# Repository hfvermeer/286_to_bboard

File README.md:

# 286 to breadboard adapter
60-pin breadboard adapter for the 286 processor in PLCC-68 package

## Features
This slim design breadboard adapter for the 286 processor features the essential connections, descriptions, decoupling capacitors and even a small array of debugging leds for the system pin outputs. 

The debugging leds are optional, and may be left unpopulated if desired. The debugging leds may be switched off too by cutting the solder jumper 'JP1', or re-enabled again by soldering the bridge. It is enabled by default.

The adapter may also use J3 to provide power pins on the bottom side that directly connect to the breadboard power lines.

## Hardware Documentation

### Connections

#### J1 - Breadboard Jumper Header 1

Pin | Description
--- | -----------
1   | HLDA
2   | <ins>PEACK</ins>
3   | COD/<ins>INT</ins>
4   | <ins>Lock</ins>
5   | M//<ins>IO</ins>
6   | <ins>BHE</ins>
7   | <ins>S1</ins>
8   | <ins>S0</ins>
9   | D15
10  | D14
11  | D13
12  | D12
13  | D11
14  | D10
15  | D9
16  | D8
17  | D7
18  | D6
19  | D5
20  | D4
21  | D3
22  | D2
23  | D1
24  | D0
25  | <ins>ERROR</ins>
26  | <ins>BUSY</ins>
27  | CLK
28  | RESET
29  | GND
30  | VCC

#### J2 - Breadboard Jumper Header 2

Pin | Description
--- | -----------
1   | HOLD
2   | PEREQ
3   | NMI
4   | INTR
5   | <ins>READY</ins>
6   | GND
7   | A23
8   | A22
9   | A21
10   | A20
11  | A19
12  | A18
13  | A17
14  | A16
15  | A15
16  | A14
17  | A13
18  | A12
19  | A11
20  | A10
21  | A9
22  | A8
23  | A7
24  | A6
25  | A5
26  | A4
27  | A3
28  | A2
29  | A1
30  | A0

#### J3 - Breadboard Jumper Header 3 (Optional)

Pin | Description
--- | -----------
1   | VCC
2   | GND

### Bill of Materials (BOM)

Component type | Reference | Description | Quantity | Source and notes
-------------- | --------- | ----------- | -------- | ----------------
Capacitor | C1, C3, C4, C5 | 100nf, 0805 | 4 | 
Capacitor | C2 | 10uf, 0805 | 1 | 
Capacitor | C6 | 47nf, 0805 | 1 |
Capacitor | C7 | 100nf, 0402 | 1 | 
LED | D1, D2. D3, D4, D5, D6, D7, D8 | RED, 0603 | 8 |
Resistor | R1, R2. R3, R4, R5, R6, R7, R8 | 2k, 0402 | 8 |
Resistor | R9 | 1k, 0402 | 1 | 
Jumper | J1, J2 | Vertical, 2.54mm, SMT, pin1 left | 2 | 
Jumper | J3 | Vertical, 2.54mm, THT | 1 | 
IC | U1 | 74HC244, TSSOP-20 | 1 | 
Socket | UA1 | PLCC-68, SMT | 1 |

### Build Instructions

Hand solder under soldering microscope. The pads for connectors J1 and J2 contain via-in-pads. If using a stencil, these must be filled with tin prior to applying paste, otherwise they may wich up solder paste that is applied.

## Release Notes

### Changes

* Version 1.0.0
  * Add component Values
  * Correct 74HC240 to 74HC244 in schematic
  * Correct label descriptions for GND, CLK, VCC and RESET
  * Add anchor plate for pin headers
  * Add Gerbers

* Version 0.9.0
  * Initial Release

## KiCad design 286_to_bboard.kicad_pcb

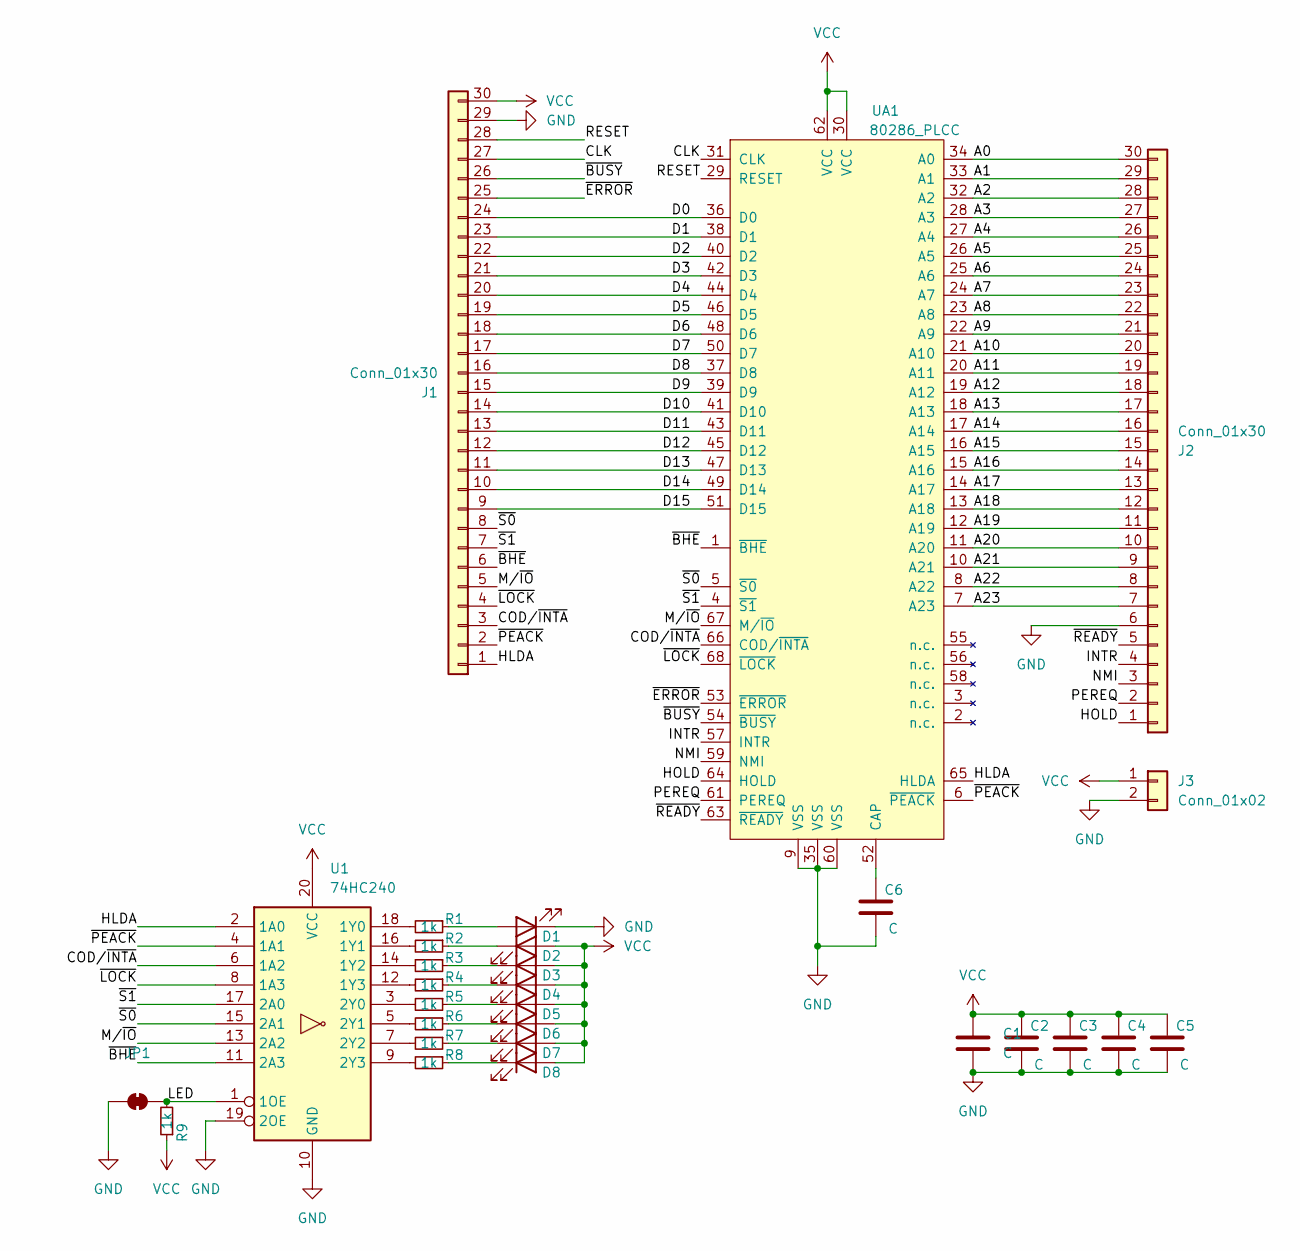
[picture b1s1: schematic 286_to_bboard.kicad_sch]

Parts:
C1, C2, C3, C4, C6: C; C_0805_2012Metric_Pad1.18x1.45mm_HandSolder
C5: C; C_0402_1005Metric_Pad0.74x0.62mm_HandSolder
D1, D2: RED; LED_0603_1608Metric
D3, D4, D5, D6, D7, D8: HLDA; LED_0603_1608Metric
J1, J2: Conn_01x30; PinHeader_1x30_P2.54mm_Vertical_SMD_Pin1Left
J3: Conn_01x02; PinHeader_1x02_P2.54mm_Vertical
JP1: Bridged; SolderJumper-2_P1.3mm_Bridged_RoundedPad1.0x1.5mm
R1, R2, R3, R4, R5, R6, R7, R8: 1k; R_0402_1005Metric
R9: 1k; R_0402_1005Metric_Pad0.72x0.64mm_HandSolder
U1: 74HC240
UA1: 80286_PLCC; PLCC-68_SMD-Socket

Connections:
/A0: J2.30, UA1.34 (A0)
/A1: J2.29, UA1.33 (A1)
/A2: J2.28, UA1.32 (A2)
/A3: J2.27, UA1.28 (A3)
/A4: J2.26, UA1.27 (A4)
/A5: J2.25, UA1.26 (A5)
/A6: J2.24, UA1.25 (A6)
/A7: J2.23, UA1.24 (A7)
/A8: J2.22, UA1.23 (A8)
/A9: J2.21, UA1.22 (A9)
/A10: J2.20, UA1.21 (A10)
/A11: J2.19, UA1.20 (A11)
/A12: J2.18, UA1.19 (A12)
/A13: J2.17, UA1.18 (A13)
/A14: J2.16, UA1.17 (A14)
/A15: J2.15, UA1.16 (A15)
/A16: J2.14, UA1.15 (A16)
/A17: J2.13, UA1.14 (A17)
/A18: J2.12, UA1.13 (A18)
/A19: J2.11, UA1.12 (A19)
/A20: J2.10, UA1.11 (A20)
/A21: J2.9, UA1.10 (A21)
/A22: J2.8, UA1.8 (A22)
/A23: J2.7, UA1.7 (A23)
/CLK: J1.27, UA1.31 (CLK)
/COD/~INTA: J1.3, U1.6 (1A2), UA1.66 (COD/~INTA)
/D0: J1.24, UA1.36 (D0)
/D1: J1.23, UA1.38 (D1)
/D2: J1.22, UA1.40 (D2)
/D3: J1.21, UA1.42 (D3)
/D4: J1.20, UA1.44 (D4)
/D5: J1.19, UA1.46 (D5)
/D6: J1.18, UA1.48 (D6)
/D7: J1.17, UA1.50 (D7)
/D8: J1.16, UA1.37 (D8)
/D9: J1.15, UA1.39 (D9)
/D10: J1.14, UA1.41 (D10)
/D11: J1.13, UA1.43 (D11)
/D12: J1.12, UA1.45 (D12)
/D13: J1.11, UA1.47 (D13)
/D14: J1.10, UA1.49 (D14)
/D15: J1.9, UA1.51 (D15)
/HLDA: J1.1, U1.2 (1A0), UA1.65 (HLDA)
/HOLD: J2.1, UA1.64 (HOLD)
/INTR: J2.4, UA1.57 (INTR)
/LED: JP1.2 (B), R9.2, U1.1 (1OE)
/M/~IO: J1.5, U1.13 (2A2), UA1.67 (M/~IO)
/NMI: J2.3, UA1.59 (NMI)
/PEREQ: J2.2, UA1.61 (PEREQ)
/RESET: J1.28, UA1.29 (RESET)
/~BHE: J1.6, U1.11 (2A3), UA1.1 (~BHE)
/~BUSY: J1.26, UA1.54 (~BUSY)
/~ERROR: J1.25, UA1.53 (~ERROR)
/~LOCK: J1.4, U1.8 (1A3), UA1.68 (~LOCK)
/~PEACK: J1.2, U1.4 (1A1), UA1.6 (~PEACK)
/~READY: J2.5, UA1.63 (~READY)
/~S0: J1.8, U1.15 (2A1), UA1.5 (~S0)
/~S1: J1.7, U1.17 (2A0), UA1.4 (~S1)
GND: C1.2, C2.2, C3.2, C4.2, C5.2, C6.2, D1.1 (K), J1.29, J2.6, J3.2, JP1.1 (A), U1.10 (GND), U1.19 (2OE), UA1.9 (VSS), UA1.35 (VSS), UA1.60 (VSS)
unnamed: D1.2 (A), R1.1
unnamed: D2.1 (K), R2.1
unnamed: D3.1 (K), R3.1
unnamed: D4.1 (K), R4.1
unnamed: D5.1 (K), R5.1
unnamed: D6.1 (K), R6.1
unnamed: D7.1 (K), R7.1
unnamed: D8.1 (K), R8.1
unnamed: R1.2, U1.18 (1Y0)
unnamed: R2.2, U1.16 (1Y1)
unnamed: R3.2, U1.14 (1Y2)
unnamed: R4.2, U1.12 (1Y3)
unnamed: R5.2, U1.3 (2Y0)
unnamed: R6.2, U1.5 (2Y1)
unnamed: R7.2, U1.7 (2Y2)
unnamed: R8.2, U1.9 (2Y3)
unnamed: C6.1, UA1.52 (CAP)
VCC: C1.1, C2.1, C3.1, C4.1, C5.1, D2.2 (A), D3.2 (A), D4.2 (A), D5.2 (A), D6.2 (A), D7.2 (A), D8.2 (A), J1.30, J3.1, R9.1, U1.20 (VCC), UA1.30 (VCC), UA1.62 (VCC)

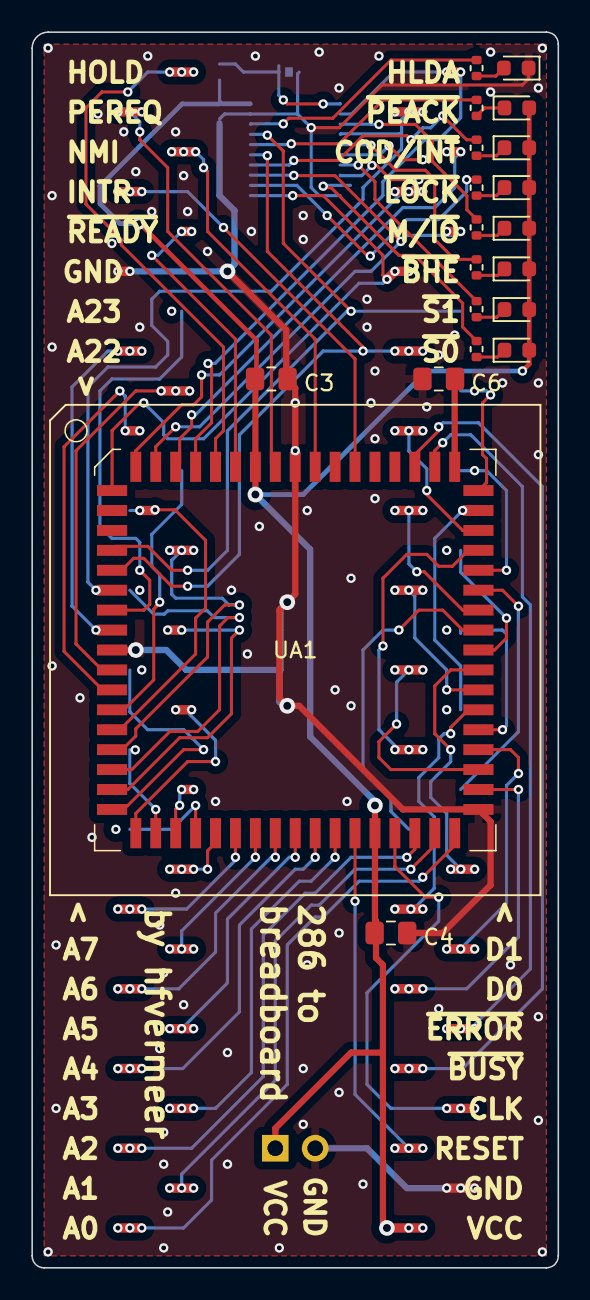
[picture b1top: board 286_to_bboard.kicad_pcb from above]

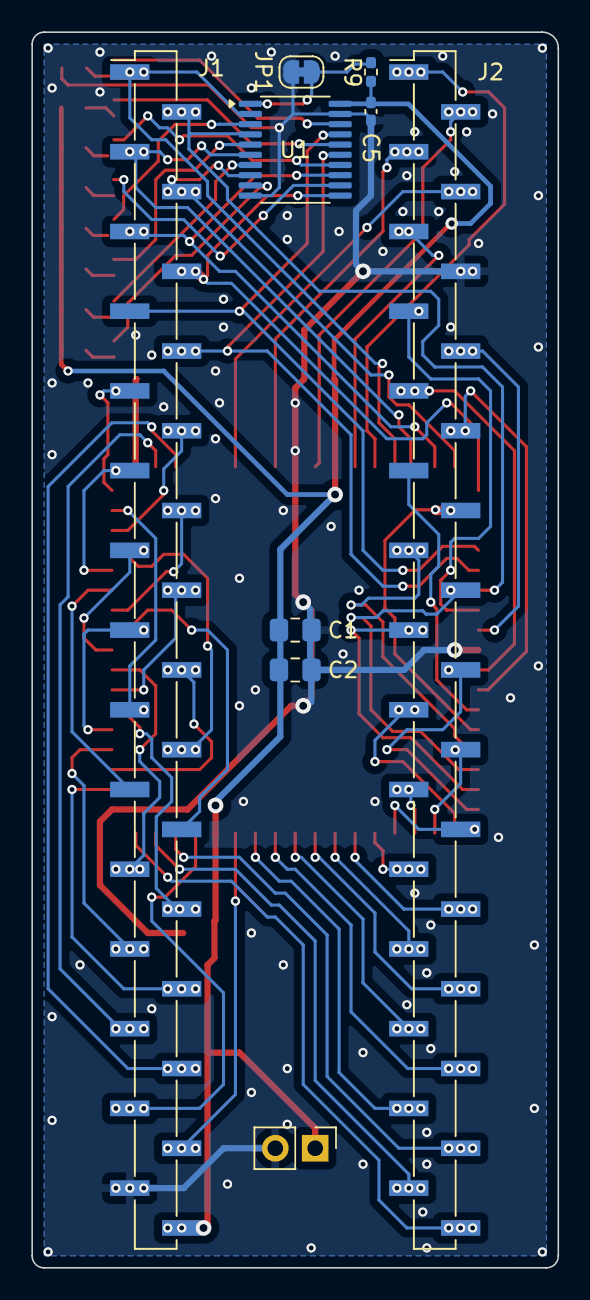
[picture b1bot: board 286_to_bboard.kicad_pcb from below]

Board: 2 copper layers, 33.5 x 78.7 mm, 29 parts (9 on the bottom side), 77 nets.

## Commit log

2025-08-12 gitignore
2025-08-12 initial layout
2025-08-12 finalize initial design
2025-08-13 strengthen headers with riveting vias
2025-08-13 add gerbers
2025-08-13 add anchor plates
2025-08-13 typo corrections and readme.md
2025-08-13 readme updates
2025-08-13 table
2025-08-13 small revisions
2025-08-13 add License
2025-08-13 release and readme updates
2025-08-13 add picture
2025-08-13 add another image
2025-08-13 migrate kicad folder
